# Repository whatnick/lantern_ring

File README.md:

# Lantern Ring

**One ring to rule them all, in the light bind them**

## v2 physical hardware

[FreeCAD v2 twist-lock hardware](hardware/v2.0/ring_3d/README.md) provides a keyed
30-degree bayonet PCB/battery cassette, opposite-face CR2032 pogo contacts,
one insulated ground lead and screw-retained battery access. The compact crown
is 24.9 mm across, with the original 11 mm band width at the crest and a **rounded open-bottom
elastic band**. Hollow 40-degree conical shoulder walls brace the crown onto the
band, as the legacy side plates did. The shank tapers to 6 mm at the open tips
with comfort-fit rounded edges, using 2.5% less material than the unbraced band. The crown nests onto the finger arc; its LED-inclusive profile
is **11.42 mm above the finger**. A
[same-scale legacy comparison](hardware/v2.0/ring_3d/generated/legacy-comparison.png)
documents the remaining height/diameter difference. Editable CAD and printable
files are included.
Battery replacement needs no soldering; the direct positive pogo and ground
lead still need three permanent joints. This is an unprinted, electrically unqualified prototype for the
mono-colour PCB, not a certified battery-powered product.
The [elastic-fit study](hardware/v2.0/ring_3d/generated/flex-fit.png) illustrates
a 1 mm expansion target, not a qualified size range; PA12 spring-back, creep
and comfortable fit still require physical testing.

### v2 CAD renders

Blender 5 assembly animation ([MP4](hardware/v2.0/ring_3d/generated/lantern_ring_v2_assembly.mp4)).

Low-profile [Lantern Corps crowns](hardware/v2.0/ring_3d/README.md#lantern-corps-crowns-low-profile-top-piece):
swappable translucent top pieces that sit 2.3 mm above the PCB (the v1 emblem stood 6.5 mm).

Crown swap animation ([MP4](hardware/v2.0/ring_3d/generated/lantern_corps_swap.mp4)),
with each crown and LED colour representing a different Corps.

| Assembled: low crown, braced open tapered band | Exploded: bayonet cassette and pogo stack |
| --- | --- |
|  |  |

| Same-scale legacy comparison | Open-band elastic-fit screen (unqualified) |
| --- | --- |
|  |  |

[Repository baseline review](docs/design/repository-review.md) distinguishes the
existing board variants and unfinished experiments.

[Contact and metal-body roadmap](docs/design/contact-roadmap/README.md) explores
copper-tape pressure contacts, replaceable plated springs and an electrically
isolated metal shell, with progressive local renders and prepared Nano Banana
prompts. These concepts do not replace the current manufacturing CAD.

[IR ring programming clip](hardware/v2.0/ring_ir_prog_clip/README.md) is a
solder-free pogo-pin ISP clip for the ATtiny85 `ring_pcb_IR`. It is a probe,
anvil and fence PCB set for an Adafruit 5434-style hinged clip kit. Its pin
spacing comes from the IR board's rear test pads, and it has a standard AVR
ISP-6 header. It passes KiCad ERC/DRC and a FreeCAD virtual fit against
estimated clip dimensions. It has not yet been built or measured.

### Experimental RGBW PCBs

The [four-single-MOSFET](hardware/v2.0/ring_pcb_RGBW/README.md) and
[two-dual-MOSFET](hardware/v2.0/ring_pcb_RGBW_dual/README.md) RGBW variants
are both routed as **four-layer, 1.6 mm** boards. Their inner layers are GND
and VCC planes; the IR outline, TP1-TP9 pads and exposed contact windows are
preserved. Saved KiCad ERC/DRC reports show zero violations, unconnected items
and schematic-parity issues. See the [routing and MOSFET comparison](docs/design/rgbw-mosfet-comparison.md).

These are virtual results, not fabrication, physical clip-fit, battery safety
or electrical qualification. [Experimental RGBW firmware](firmware/rgbw-driver/README.md)
provides fixed and JP1-selected colours but has not been tested on hardware.
The redesigned RGBW LED is active; confirm stock and assembly sourcing before ordering.

The [Elecrow 3D-print feasibility assessment](docs/design/elecrow-3d-print-feasibility.md)
covers fit risks for the ring's non-PCB components.

The [Lantern Ring pricing and market feasibility analysis](docs/design/product-market-analysis.md)
documents the unit-cost assumptions, price tests, event-market scenarios and
commercial readiness gates.

Engineering source references and regeneration instructions are in
[development.md](development.md).
| 1. Serviceable pogo | 2. Copper pressure | 3. Plated springs | 4. Floating metal |
| --- | --- | --- | --- |
|  |  |  |  |

## Legacy printed ring bodies

These are earlier printed ring bodies and emblem pieces, not the v2 twist-lock
cassette. The [legacy ring-body and emblem models](hardware/v1.0/ring_3d/) are
preserved alongside the newer design.

Available on :
- [Tindie](https://www.tindie.com/products/whatnick/lantern-rings/)
- [Etsy](https://www.etsy.com/au/listing/1365896916/lantern-corps-cosplay-ring-with)
- [PCBWay]
- [OSHPark]
- [Aisler](https://aisler.net/p/UOBXJDJP)
- [Shapeway](https://www.shapeways.com/shops/whatnick)
  - [Ring body](https://www.shapeways.com/product/PLQWLUV6V/lantern-ring-body?optionId=251926151&li=shop-inventory)
  - [Green Lantern Logo](https://www.shapeways.com/product/PLQWLUV6V/lantern-ring-body?optionId=251926155&li=shop-inventory)
  - [Yellow Lantern Logo](https://www.shapeways.com/product/87AK6SYQN/yellow-fear-lanterns-logo-from-dc-universe?optionId=253809626&li=shops)
  - [Blue Lantern Logo](https://www.shapeways.com/product/LDGX3RYWW/hope-lanterns-logo-from-dc-universe?optionId=253809602&li=shops)
  - [Indigo Lantern Logo](https://www.shapeways.com/product/RX6YYCM8E/indigo-empathy-logo-from-dc-universe?optionId=253810127&li=shops)
  - [Violet Lantern Logo](https://www.shapeways.com/product/Q4ZM3RG58/purple-love-lanterns-logo?optionId=253810197&li=shops)
  - [Red Lantern Logo](https://www.shapeways.com/product/2T2WC596J/red-rage-lanterns-logo?optionId=253810042&li=shops)
  - [Orange Lantern Logo](https://www.shapeways.com/product/XHF33N3QN/orange-avarice-lanterns-logo?optionId=253810121&li=shops)
  - [Black Lantern Logo](https://www.shapeways.com/product/NEF64B7SB/lantern-ring-life-and-death)
  - [White Lantern Logo](https://www.shapeways.com/product/NEF64B7SB/lantern-ring-life-and-death)
  - [Black MTG Logo](https://www.shapeways.com/product/NJ25J3LPM/magic-the-gathering-black-mana-logo?optionId=253809132)

[LED Colours and quantum physics](https://www.forbes.com/sites/chadorzel/2019/07/01/the-mostly-quantum-physics-of-making-colors/?sh=2ce5846e3953) are inextricably linked.
After watching a temperature based LED colour changing demo at questacon, an idea started forming in my head for using a similar idea with LED's of different colours and seeing how they
react spectrally with temperature.

I have also always been a Green Lantern nerd and I have been making lantern rings since 2010. You will probably find some of them in the wild in Hobart among the clientele of various
pubs and nightclubs. This is a more serious attempt at making a piece of electronic jewellery, cosplay prop and nerdy onanism all rolled into one.

## Licence

[OSHW TAPR](https://tapr.org/the-tapr-open-hardware-license/)

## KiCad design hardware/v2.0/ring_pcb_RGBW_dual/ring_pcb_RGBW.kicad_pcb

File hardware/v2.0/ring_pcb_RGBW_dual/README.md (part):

# Lantern Ring v2 RGBW variant: dual MOSFET option

**Experimental RGBW hardware, not physically qualified.** This generated KiCad
10 project uses one four-die RGBW LED and four MOSFET-driven channels using
two dual N-channel MOSFET packages. It keeps the IR board's native outline,
1.6 mm thickness and TP1-TP9 interface. The RGBW
variant uses **four copper layers**, unlike the two-layer IR board: dedicated
In1 GND and In2 VCC planes avoid relying on fragmented outer pours.
The IR board, programming clip and legacy firmware remain unchanged.

This **routed four-layer** option's saved all-severity KiCad reports show zero
ERC/DRC findings, unconnected items and schematic-parity issues. The separately
retained [four-single-MOSFET option](../ring_pcb_RGBW/README.md) is the
comparison baseline. Both are experimental and neither has been physically
qualified.
[See the routed/electrical comparison](../../../docs/design/rgbw-mosfet-comparison.md).

[Schematic PDF](generated/schematic.pdf) |
[Top render](generated/top.png) | [Rear render](generated/bottom.png) |
[Top routing](generated/top_routing.svg) |
[Rear routing, mirrored for viewing](generated/bottom_routing.svg) |
[Inner GND](generated/ground_plane.svg) | [Inner VCC](generated/supply_plane.svg) |
[Validation evidence](generated/validation.json)

## Fixed mechanical and programming interface

Use the native [IR PCB](../ring_pcb_IR/ring_pcb_IR.kicad_pcb) as the exact
interface source, not a redraw or an assumed circular envelope.

- Preserve all Edge.Cuts geometry, board thickness (1.6 mm), origin and
  orientation. Do not resize or mirror the board.
- Preserve TP1-TP9 positions, pad shapes/sizes, copper sides, exposed mask
  geometry and electrical assignments, including front TP8 GND for the anvil.
  PB3/PB4 becoming application signals does not change TP4/TP5 assignments.
- Preserve the rear pogo grid (3.05 mm) and off-grid TP9 VCC. Do not substitute
  the ISP header's 2.54 mm pitch for the pogo spacing.
- Reuse the existing [v0.2 programming clip](../ring_ir_prog_clip/README.md)
  and [ArduinoISP harness](../ring_ir_prog_clip/programming.md) without
  rewiring. J1 pins 1-6 remain MISO, VCC, SCK, MOSI, RESET, GND.
- Keep rear contact areas clear of components and preserve front anvil
  contact/clearance regions. The new LED and MOSFET envelopes must be checked
  against the clip window and jaws; matching the outline alone does not prove fit.

The existing [board-layer export](../ring_ir_prog_clip/generated/assembly/ir_board_layers.json)
and [clip geometry](../ring_ir_prog_clip/generated/geometry.json) document
the current interface. The native IR board is authoritative if exports differ.
Do not regenerate the clip to accommodate moved RGBW programming pads.

## ATtiny85 pin allocation

Keep the internal oscillator and PB5 RESET enabled so the same ISP clip works.
The ATtiny85 has three usable independent hardware-PWM output pins for this
allocation, not four: Timer1's complementary outputs are not extra independent
colour channels.

| MCU pin | Existing pad | Circuit use | PWM or input |
| --- | --- | --- | --- |
| PB0 | TP1 / MOSI | Red MOSFET gate | Hardware OC0A |
| PB1 | TP2 / MISO | Green MOSFET gate | Hardware OC0B |
| PB2 | TP3 / SCK | White MOSFET gate | Timer-driven software PWM |
| PB3 | TP4 | Optional colour/mode selector | Digital input or ADC3 |
| PB4 | TP5 | Blue MOSFET gate | Hardware OC1B |
| PB5 | TP6 / RESET | ISP reset only | Do not reclaim as GPIO |
| GND | TP7, TP8 | Ground; TP8 is the anvil contact | Unchanged |
| VCC | TP9 | Programming supply | Unchanged |

Yes, a jumper can select colour: PB3 with a pull-up and a separate jumper or
solder bridge to GND provides two selectable presets/modes. Do not alter the
TP4 pogo pad to make the selector. More choices could use a resistor-coded
ADC3 input with defined voltage bands; this needs tolerance/noise validation.
Read/latch the selector before starting PWM and never leave the input floating.
Without a selector, new firmware can define the palette and sweep behaviour.

Reference: [manufacturer ATtiny25/45/85 datasheet, 2586Q](https://ww1.microchip.com/downloads/en/DeviceDoc/Atmel-2586-AVR-8-bit-Microcontroller-ATtiny25-ATtiny45-ATtiny85_Datasheet.pdf),
Table 10-3, page 60. PB4 is OC1B; PB3 is its complementary output and ADC3.
Timer1 OC1A shares PB1, already used by OC0B. PB2 has no hardware PWM output.

## Implemented circuit

The [QT Brightek QBLP679-RGBCW](https://www.qt-brightek.com/datasheet/QBLP679-RGBXW.pdf)
has four independent dies, not an internally common anode. Copper connects
R/G/B/W anodes 5/6/7/8 to VCC; their cathodes are 4/3/2/1. This gives
common-anode circuit operation with the existing low-side N-MOSFETs. The
5 x 5 x 1.65 mm package has a 5.5 mm lead span; the footprint follows the
manufacturer's page 11 land pattern. Page 4 brightness specifications are
at 20 mA and do not predict this design's sub-mA brightness or colour.

On 22 November 2026 DigiKey listed this exact part active and in stock in cut
tape; JLCPCB listed it out of stock. Recheck availability, MSL 5A handling,
assembly sourcing and current price before ordering.

Each cathode connects through a **2.2k, 1%, 63 mW 0402** resistor to one
channel of an onsemi **NTZD3154NT1G** dual N-channel MOSFET (SOT-563).
Q1 drives R/G and Q2 drives B/W. Each source goes to GND; every gate retains
its own 1k series resistor and 100k pull-down. Onsemi specifies RDS(on) maximum
0.9 ohm at VGS 1.8 V/ID 350 mA and absolute VGS +/-7 V. Pin mapping is
1=S1, 2=G1, 3=D2, 4=S2, 5=G2, 6=D1; verify the manufacturer pinout before
substitution. The manufacturer lists NTZD3154NT1G active in its ordering table
but marks some other suffixes discontinued; confirm actual purchasing status.
The MCU is **ATTINY85-20MU**, with 100n X7R 10 V local bypass, 10u X5R 10 V
bulk capacitance and a 10k RESET pull-up. The [BOM](generated/bom.csv) records
MPNs and distributor search links, not stock or purchase approval.

JP1 is a separate, normally open **0402 bridge footprint**: short it with a
0-ohm 0402 link or a deliberate solder bridge to pull PB3 low. Its external
100k pull-up defines the open state. It is not a fitted pin header and does
not modify TP4. Two settings select two firmware-defined presets/modes; an
ADC ladder for more choices is not implemented.

At the maximum intended 5.5 V bench supply, even a shorted die is bounded by
`5.5 / (2200 * 0.99) = 2.526 mA` per channel. Maximum resistor dissipation is
13.9 mW, below 63 mW. These are conservative electrical bounds, **not CR2032
load/temperature qualification**. ISP can switch the R/G/W gates while RESET
is asserted; firmware cannot prevent that. The resistors remain in circuit.
Use one regulated 5 V programming supply with matching logic levels; remove
the CR2032, never backfeed or charge it. Do not apply 5 V while a cell is fitted.

There is **no boost converter or constant-current driver**. Blue/green/white
may dim or extinguish as the cell discharges. Measure brightness, simultaneous
channel current, battery life and temperatures before treating this as usable
jewellery. The NTZD3154N gate network also loads the ISP signals; verify actual
programming on the new assembled variant rather than inheriting the IR result.

## Firmware boundary

- The working 5 V programming report applies to the IR board, not automatically
  this RGBW circuit. Check every new component, LED current limiter and rail for
  the 5 V programming case. Remove the CR2032; never join programming and cell
  supplies or charge the cell.
- Budget total LED/MCU current for a primary CR2032, including simultaneous
  colours. Its resistance is not a current limiter. Blue/green/white forward
  voltage may leave insufficient regulation headroom as the cell discharges;
  determine whether a boost rail is needed before choosing parts.
- Use new RGBW firmware, not edits to Arduino-TV-B-Gone. Preserve timer ownership
  for three hardware channels and timer-driven software PWM on PB2; validate
  PWM frequency, endpoint duties, core timing interactions and colour mixing.
  Keep PB3 configured as an input and preserve RESET/SPI fuses.

An [experimental RGBW driver](../../../firmware/rgbw-driver/README.md) now
provides a fixed firmware colour or two JP1-selected presets. It has not been
flashed or validated on this PCB. Validate polarity, frequencies, endpoint
duties, current and selector latching on real hardware.

## Sources, rebuild and checks

`parameters.json` defines placements, channel/pin mapping, exact LED lands,
critical VCC/PB2 routes and via positions. `generate.py` reads the native IR board,
generates the schematic and exports KiCad's actual XML netlist before assigning
PCB nets. Edit these sources, **not generated KiCad files**. `finish_route.py`
requires the matching placement/DSN and imports the local SES before refilling
and checking the saved board with KiCad. No electrical-rule exclusions are used.
The four-layer stack must be fabricated at 1.6 mm finished thickness.

```powershell
# Verify saved work without discarding routing:
& hardware\v2.0\ring_pcb_RGBW_dual\build.ps1

# Complete regeneration, local routing, CAD and actual-board renders:
& hardware\v2.0\ring_pcb_RGBW_dual\build.ps1 -Rebuild -Render -FreeroutingJar 'C:\tools\freerouting-2.5.0.jar'

python -m unittest discover -s hardware\v2.0\ring_pcb_RGBW_dual -p test_rgbw.py
```

Requires KiCad 10, FreeCAD's bundled Python and Java for regeneration.
Paths can be overridden with the build parameters. Freerouting 2.5.0 runs
locally with analytics, API and MCP servers off and isolated settings.
The generator first connects supply pads to the inner planes with checked
0.25 mm stubs and places the constrained PB2/SCK escape. The build rejects
any unconnected GND/VCC item before routing. Autorouting handles the remaining
signals; it skips the already connected Power class. This is not a native
electrical-rule exclusion. Router fanout, optimization and automatic neck-down
are disabled; final native DRC rejects any route narrower than 0.15 mm.
Power is 0.25 mm; through-vias are 0.45/0.20 mm diameter/drill.
The footprint is assembly-dense: references use 0.6 mm text/0.12 mm stroke
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
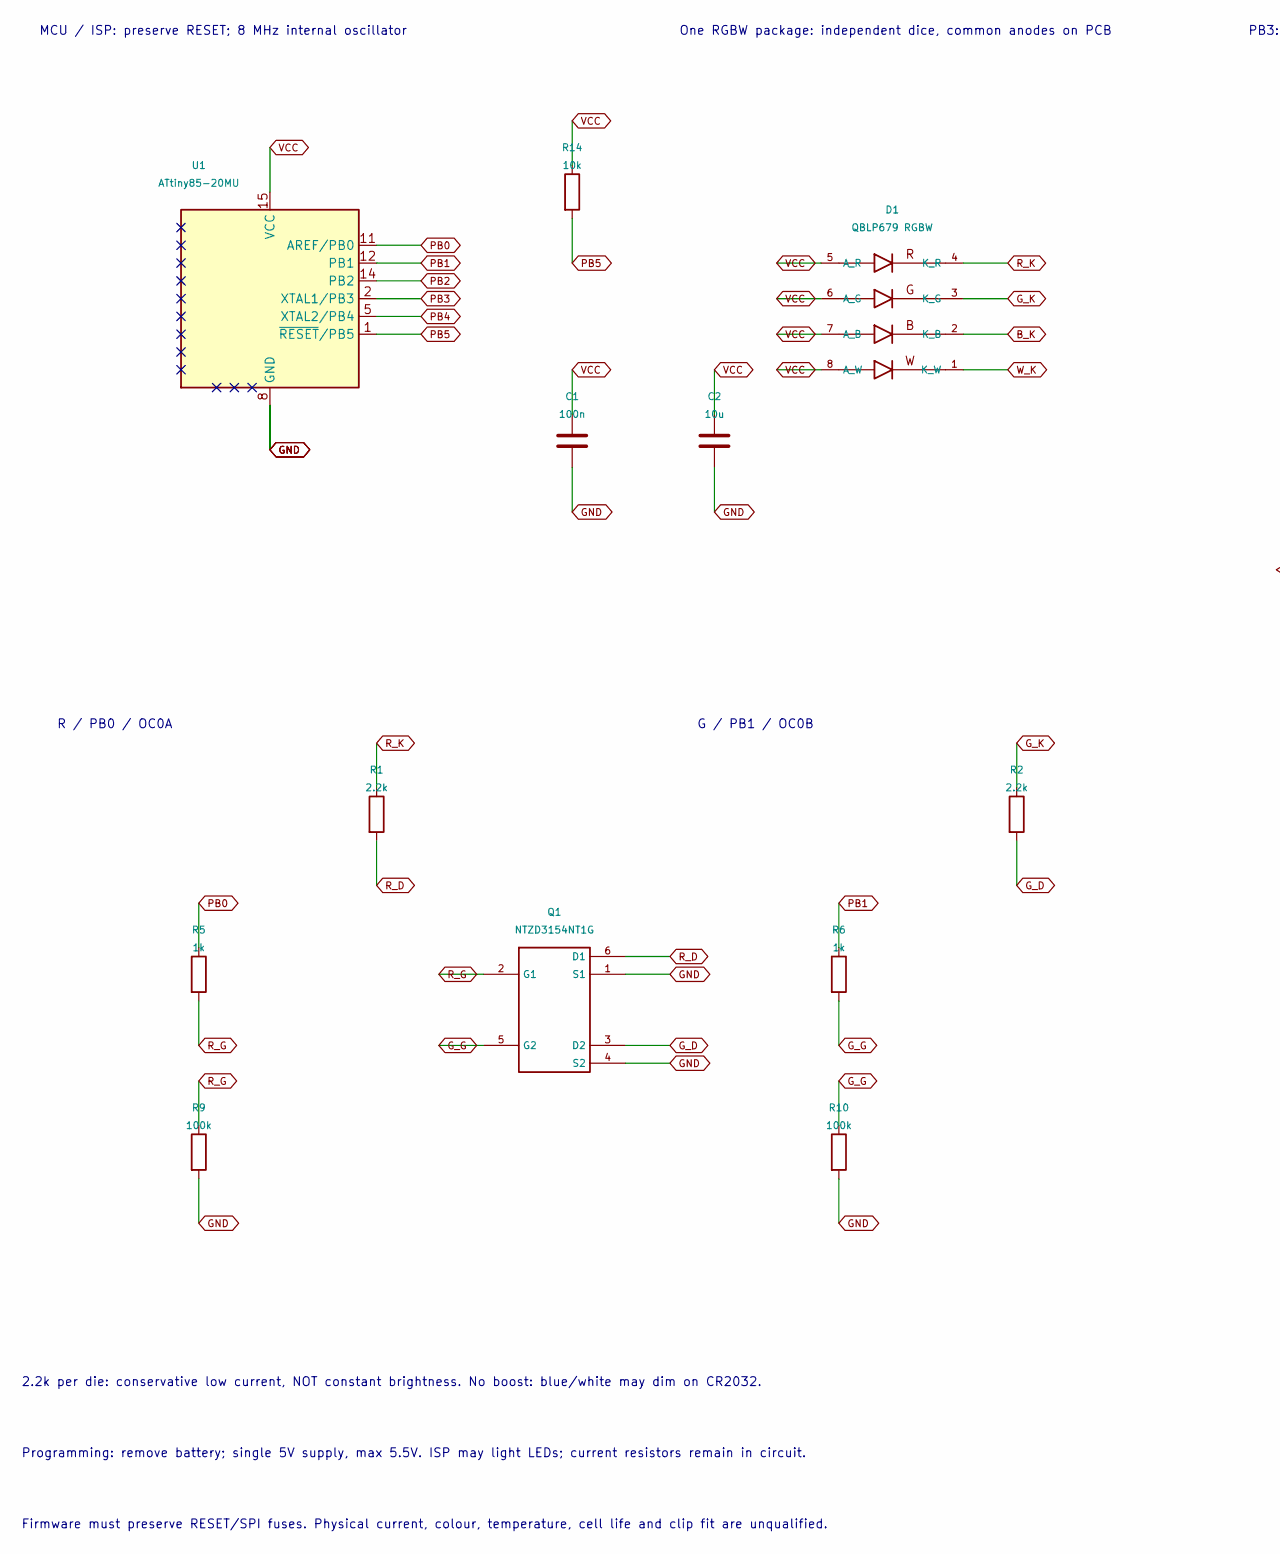
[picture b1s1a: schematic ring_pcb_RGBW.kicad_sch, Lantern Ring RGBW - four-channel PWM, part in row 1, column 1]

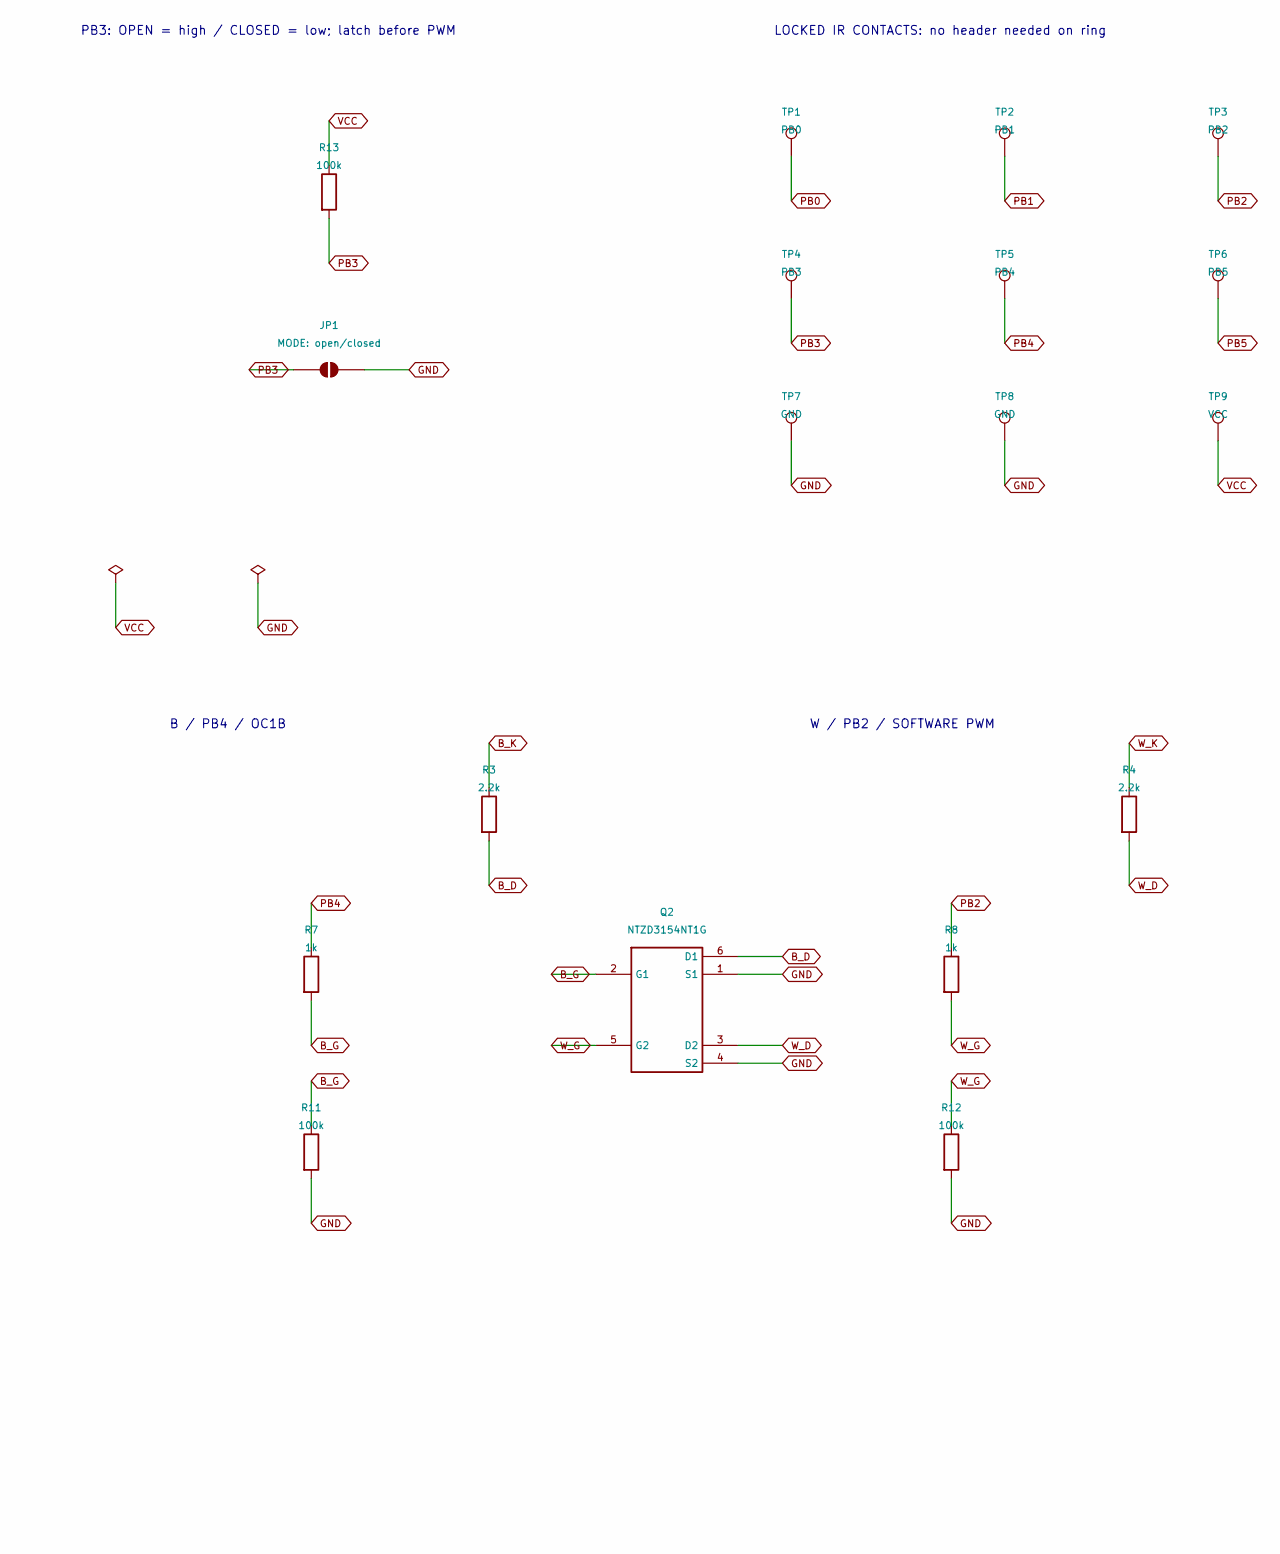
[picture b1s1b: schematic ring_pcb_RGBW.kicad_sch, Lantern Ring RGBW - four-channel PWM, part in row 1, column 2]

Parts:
C1: 100n; C0402; MPN GRM155R71A104KA01D
C2: 10u; C0805; MPN CL21A106KPFNNNE
D1: QBLP679 RGBW; QBLP679_PLCC8; MPN QBLP679-RGBCW
JP1: MODE: open/closed; ModeBridge
Q1, Q2: NTZD3154NT1G; SOT563; MPN NTZD3154NT1G
R1, R2, R3, R4: 2.2k; R0402; MPN RC0402FR-072K2L
R5, R6, R7, R8: 1k; R0402; MPN RC0402FR-071KL
R9, R10, R11, R12, R13: 100k; R0402; MPN RC0402FR-07100KL
R14: 10k; R0402; MPN RC0402FR-0710KL
TP1: PB0; IR_TP1
TP2: PB1; IR_TP2
TP3: PB2; IR_TP3
TP4: PB3; IR_TP4
TP5: PB4; IR_TP5
TP6: PB5; IR_TP6
TP7: GND; IR_TP7
TP8: GND; IR_TP8
TP9: VCC; IR_TP9
U1: ATtiny85-20MU; QFN20; MPN ATTINY85-20MU

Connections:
B_D: Q2.6 (D1), R3.2
B_G: Q2.2 (G1), R7.2, R11.1
B_K: D1.2 (K_B), R3.1
GND: C1.2, C2.2, JP1.2 (B), Q1.1 (S1), Q1.4 (S2), Q2.1 (S1), Q2.4 (S2), R9.2, R10.2, R11.2, R12.2, TP7.1, TP8.1, U1.8 (GND), U1.21 (GND)
G_D: Q1.3 (D2), R2.2
G_G: Q1.5 (G2), R6.2, R10.1
G_K: D1.3 (K_G), R2.1
PB0: R5.1, TP1.1, U1.11 (AREF/PB0)
PB1: R6.1, TP2.1, U1.12 (PB1)
PB2: R8.1, TP3.1, U1.14 (PB2)
PB3: JP1.1 (A), R13.2, TP4.1, U1.2 (XTAL1/PB3)
PB4: R7.1, TP5.1, U1.5 (XTAL2/PB4)
PB5: R14.2, TP6.1, U1.1 (~RESET/PB5)
R_D: Q1.6 (D1), R1.2
R_G: Q1.2 (G1), R5.2, R9.1
R_K: D1.4 (K_R), R1.1
VCC: C1.1, C2.1, D1.5 (A_R), D1.6 (A_G), D1.7 (A_B), D1.8 (A_W), R13.1, R14.1, TP9.1, U1.15 (VCC)
W_D: Q2.3 (D2), R4.2
W_G: Q2.5 (G2), R8.2, R12.1
W_K: D1.1 (K_W), R4.1

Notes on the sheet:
MCU / ISP: preserve RESET; 8 MHz internal oscillator
One RGBW package: independent dice, common anodes on PCB
PB3: OPEN = high / CLOSED = low; latch before PWM
LOCKED IR CONTACTS: no header needed on ring
R / PB0 / OC0A
G / PB1 / OC0B
B / PB4 / OC1B
W / PB2 / SOFTWARE PWM
2.2k per die: conservative low current, NOT constant brightness. No boost: blue/white may dim on CR2032.
Programming: remove battery; single 5V supply, max 5.5V. ISP may light LEDs; current resistors remain in circuit.
Firmware must preserve RESET/SPI fuses. Physical current, colour, temperature, cell life and clip fit are unqualified.

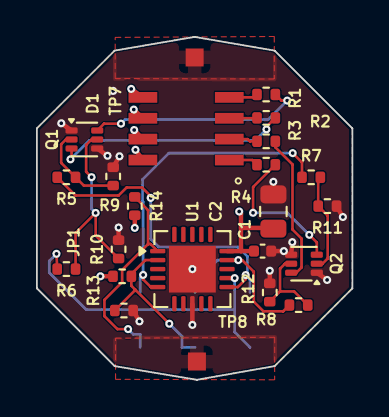
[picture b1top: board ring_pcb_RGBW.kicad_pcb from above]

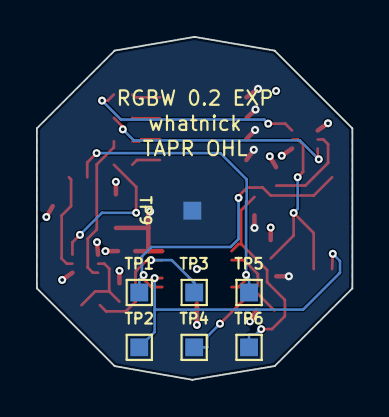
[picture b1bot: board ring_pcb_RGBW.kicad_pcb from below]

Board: 4 copper layers, 17.5 x 19.1 mm, 30 parts (7 on the bottom side), 20 nets.

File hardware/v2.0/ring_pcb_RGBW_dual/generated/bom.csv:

Reference,Value,Footprint,Manufacturer,MPN,Description,DigiKey,Mouser,Datasheet
U1,ATtiny85-20MU,ring_rgbw:QFN20,Microchip,ATTINY85-20MU,"ATtiny85 8KB, QFN20 exposed pad, 2.7-5.5 V",https://www.digikey.com/en/products?keywords=ATTINY85-20MU,https://www.mouser.com/c/?q=ATTINY85-20MU,https://ww1.microchip.com/downloads/en/DeviceDoc/Atmel-2586-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
D1,QBLP679 RGBW,ring_rgbw:QBLP679_PLCC8,QT Brightek,QBLP679-RGBCW,"Four independent dies, anodes joined on PCB; 5.0x5.0x1.65 mm",https://www.digikey.com/en/products?keywords=QBLP679-RGBCW,https://www.mouser.com/c/?q=QBLP679-RGBCW,https://www.qt-brightek.com/datasheet/QBLP679-RGBXW.pdf
R1,2.2k,ring_rgbw:R0402,YAGEO,RC0402FR-072K2L,R die current limiter; 0402 1% 63mW,https://www.digikey.com/en/products?keywords=RC0402FR-072K2L,https://www.mouser.com/c/?q=RC0402FR-072K2L,
R5,1k,ring_rgbw:R0402,YAGEO,RC0402FR-071KL,R gate/ISP isolation; 0402 1% 63mW,https://www.digikey.com/en/products?keywords=RC0402FR-071KL,https://www.mouser.com/c/?q=RC0402FR-071KL,
R9,100k,ring_rgbw:R0402,YAGEO,RC0402FR-07100KL,R gate pull-down; 0402 1% 63mW,https://www.digikey.com/en/products?keywords=RC0402FR-07100KL,https://www.mouser.com/c/?q=RC0402FR-07100KL,
R2,2.2k,ring_rgbw:R0402,YAGEO,RC0402FR-072K2L,G die current limiter; 0402 1% 63mW,https://www.digikey.com/en/products?keywords=RC0402FR-072K2L,https://www.mouser.com/c/?q=RC0402FR-072K2L,
R6,1k,ring_rgbw:R0402,YAGEO,RC0402FR-071KL,G gate/ISP isolation; 0402 1% 63mW,https://www.digikey.com/en/products?keywords=RC0402FR-071KL,https://www.mouser.com/c/?q=RC0402FR-071KL,
R10,100k,ring_rgbw:R0402,YAGEO,RC0402FR-07100KL,G gate pull-down; 0402 1% 63mW,https://www.digikey.com/en/products?keywords=RC0402FR-07100KL,https://www.mouser.com/c/?q=RC0402FR-07100KL,
R3,2.2k,ring_rgbw:R0402,YAGEO,RC0402FR-072K2L,B die current limiter; 0402 1% 63mW,https://www.digikey.com/en/products?keywords=RC0402FR-072K2L,https://www.mouser.com/c/?q=RC0402FR-072K2L,
R7,1k,ring_rgbw:R0402,YAGEO,RC0402FR-071KL,B gate/ISP isolation; 0402 1% 63mW,https://www.digikey.com/en/products?keywords=RC0402FR-071KL,https://www.mouser.com/c/?q=RC0402FR-071KL,
R11,100k,ring_rgbw:R0402,YAGEO,RC0402FR-07100KL,B gate pull-down; 0402 1% 63mW,https://www.digikey.com/en/products?keywords=RC0402FR-07100KL,https://www.mouser.com/c/?q=RC0402FR-07100KL,
R4,2.2k,ring_rgbw:R0402,YAGEO,RC0402FR-072K2L,W die current limiter; 0402 1% 63mW,https://www.digikey.com/en/products?keywords=RC0402FR-072K2L,https://www.mouser.com/c/?q=RC0402FR-072K2L,
R8,1k,ring_rgbw:R0402,YAGEO,RC0402FR-071KL,W gate/ISP isolation; 0402 1% 63mW,https://www.digikey.com/en/products?keywords=RC0402FR-071KL,https://www.mouser.com/c/?q=RC0402FR-071KL,
R12,100k,ring_rgbw:R0402,YAGEO,RC0402FR-07100KL,W gate pull-down; 0402 1% 63mW,https://www.digikey.com/en/products?keywords=RC0402FR-07100KL,https://www.mouser.com/c/?q=RC0402FR-07100KL,
Q1,NTZD3154NT1G,ring_rgbw:SOT563,onsemi,NTZD3154NT1G,Dual low-side MOSFET; Rds max 0.9 ohm at Vgs=1.8 V,https://www.digikey.com/en/products?keywords=NTZD3154NT1G,https://www.mouser.com/c/?q=NTZD3154NT1G,https://www.onsemi.com/pdf/datasheet/ntzd3154n-d.pdf
Q2,NTZD3154NT1G,ring_rgbw:SOT563,onsemi,NTZD3154NT1G,Dual low-side MOSFET; Rds max 0.9 ohm at Vgs=1.8 V,https://www.digikey.com/en/products?keywords=NTZD3154NT1G,https://www.mouser.com/c/?q=NTZD3154NT1G,https://www.onsemi.com/pdf/datasheet/ntzd3154n-d.pdf
R13,100k,ring_rgbw:R0402,YAGEO,RC0402FR-07100KL,Mode selector pull-up; 0402 1% 63mW,https://www.digikey.com/en/products?keywords=RC0402FR-07100KL,https://www.mouser.com/c/?q=RC0402FR-07100KL,
R14,10k,ring_rgbw:R0402,YAGEO,RC0402FR-0710KL,ISP RESET pull-up; 0402 1% 63mW,https://www.digikey.com/en/products?keywords=RC0402FR-0710KL,https://www.mouser.com/c/?q=RC0402FR-0710KL,
C1,100n,ring_rgbw:C0402,Murata,GRM155R71A104KA01D,100nF X7R 10V 0402 local decoupling,https://www.digikey.com/en/products?keywords=GRM155R71A104KA01D,https://www.mouser.com/c/?q=GRM155R71A104KA01D,
C2,10u,ring_rgbw:C0805,Samsung Electro-Mechanics,CL21A106KPFNNNE,10uF X5R 10V 0805 bulk; verify DC bias,https://www.digikey.com/en/products?keywords=CL21A106KPFNNNE,https://www.mouser.com/c/?q=CL21A106KPFNNNE,

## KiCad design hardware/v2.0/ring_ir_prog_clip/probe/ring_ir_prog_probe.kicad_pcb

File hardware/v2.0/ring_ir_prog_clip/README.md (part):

# Ring IR programming clip

[Illustrated HTML wiring and voltage-testing reference](../../../docs/arduino-isp-wiring-reference.html)
contains the PDF's cable map, physical parts, Arduino IDE setup and front-side
C1/C2 checks. Open the downloaded HTML in a browser with its `docs/images` assets.

A solder-free in-system programming (ISP) clip for the
[`ring_pcb_IR`](../ring_pcb_IR) ATtiny85 board. Spring-loaded pogo pins press on
the board's rear test pads, held by a hinged clip like
[Adafruit 5434](https://www.adafruit.com/product/5434) but with pin spacing
matched to the ring. The parts are the jaws, spring and hardware from the
[AliExpress DIY pogo clip kit](https://www.aliexpress.com/item/1005006153573416.html),
with its generic guide PCBs replaced by the boards here.

> **Status: custom IR clip built and physical fit tested (user-reported).**
> ERC and DRC pass with zero violations of any severity. The FreeCAD fit check
> passes against a clip model built from **photo and datasheet estimates**,
> because the seller publishes no drawing. The AliExpress kit has now been
> assembled and photographed with calipers. The new reconstruction below uses
> readable measurements, but mounting geometry and spring travel remain estimates.
> New album photographs show the assembled custom clip with the IR PCB seated.
> No measured fit dimensions or contact-quality data have been recorded yet.
> A 2026-11-10 ATtiny85 programming run completed with full flash readback
> verification after contact alignment. The user reports the 5 V target rail
> working in practice; the documented Uno harness now uses 5 V power.
> This does not qualify contact life, LED current/temperature or mechanical
> retention; the original PCB fit report remains a virtual estimate.

## In-place minor revision

v0.2 **overwrites the existing design paths**, not a second versioned project:
`probe/ring_ir_prog_probe.kicad_pcb`, `anvil/ring_ir_prog_anvil.kicad_pcb` and
`fence/ring_ir_prog_fence.kicad_pcb`, with the existing probe/anvil schematics
and projects. Keep these names; do not create parallel `v0.2` files/directories.
The screws and balanced GND pads are a minor revision of the same assembly,
not a changed ISP pinout. Edit the generator/configuration and rebuild in place.
Git history preserves earlier revisions; old photos/quote packages remain historical.

[Recorded programming evidence](programming-evidence.json) and the
[`lantern-ring-ir-programming` skill](../../../.github/skills/lantern-ring-ir-programming/SKILL.md)
document the actual successful flow.

## As-built clip with IR PCB

The latest user-supplied photographs in the
[Clip Programmer Assembly album](https://photos.google.com/share/AF1QipNwx2ELJVqs2tECPYQ5cwoX293osVatVeGoo2XyBIm2Dzrf3vpLs3F5LxYhLjrQvA?key=RVRZOGVPc3RqZ1FpdEt0eEJ4c1piN01uNm1QZm9n),
reviewed on 2026-11-10, show the purple probe/guide PCBs assembled on the clip,
the IR board seated rear-side up in the lower locator, and pogo tips meeting
the visible rear test-pad region, including the off-grid VCC pad.
These are photographs of hardware, not CAD renders.

| Rear test-pad close-up | Off-grid VCC and signal-pad close-up |
| --- | --- |
|  |  |

The pictures support the reported physical assembly and seating; they do not
establish every tip's alignment, contact resistance, preload, retention or
successful programming. J1's SMD header lands are visibly unpopulated in these
three earlier views, so they are not evidence of a complete programmer connection. The photographed PCB
revision is not verified, and these images do not validate the new v0.2
anvil/fence screw holes or paired GND contacts. Their source URLs and downloaded
file hashes are preserved in [image provenance](images/sources.json).
No CAD dimensions or measured/unmeasured flags were changed from these views.

The newer photograph below shows the Uno, loose programming cable and the clip
with its J1 header fitted. The female leads are **not plugged into the clip**.
Use the [colour-coded harness diagrams and editable Fritzing sketch](programming.md#colour-coded-arduinoisp-harness)
to wire by signal and pin number, not by guessing colours from the photograph.

## Kit assembly animation

[Assembly video (MP4)](generated/assembly/clip_assembly.mp4) shows the lower jaw,
compression spring, upper jaw, hinge, grip block, guide/probe PCBs, screws/nuts,
pogo pins and header coming together, separating, and opening at the hinge.
The main assembly/explosion now uses the **actual custom IR adapter with SMD
header**, not a generic stock probe. A separate comparison shows
**1.27, 2.00 and 2.54 mm** stock-grid studies.
Fine-pitch pins require different guide drills; do not force large pins into them.
The flights apart identify parts, not a collision-verified tool-access sequence.
The final segment shows the **actual KiCad IR PCB copper, solder-mask openings
and silkscreen**, lifted clear for inspection and then seated LEDs-down in the
custom adapter. Component boxes remain clearance envelopes, not detailed package
models.

The custom-adapter segment separates the **actual probe, second probe/guide,
anvil and fence PCBs**, using KiCad-exported STEP substrates and the actual
top-side **SMD 2x3 male header** model, with KiCad copper, mask and silkscreen.
Its 2.54 mm mating posts accept female Dupont programming leads; there are no
header tails projecting below the probe. The pogo pattern remains unchanged.
The black service loop shows the required ground connection:
**ISP J1.6 → probe J2 → insulated wire → anvil J1 → ENIG P8 → front TP8**.
Its flexible shape is illustrative, not a cable-clearance simulation.
PB3/PB4 remain spare, unconnected positions on the probe.

**A stock 2.54 mm pogo grid is not a direct match to this IR board.** Its signal
test pads are on a **3.05 mm grid**, VCC is off-grid, and ground is on the front.
The 2.54 mm AVR ISP *header* pitch must not be confused with pogo spacing.
FreeCAD places a centred 2.54 mm grid optimistically over six pads: outer pin
centres miss by 0.51 mm across and 0.255 mm along the rows (0.570 mm diagonally).
The outer tip faces overlap only about 40% of the nominal pads; this is not
a dependable contact. Extra stock pins and wiring are not assumed safe.
Use the custom seven-pin probe/guide plus the front-ground anvil, not stock PCBs.
Rechecked directly with KiCad's board API: TP1/TP3/TP5 X coordinates are
139.6004/136.5504/133.5004 mm; TP1/TP2 Y coordinates are
115.7986/118.8486 mm. Both differences are **3.0500 mm**. Pads are 1.00 mm square,
so the edge-to-edge gap is 2.05 mm, not 2.54 mm. The reported approximately
2.5 mm physical reading does not match these centre coordinates; confirm the
physical board revision and repeat across multiple centres before changing
the manufactured adapter. The PCB and pad positions have not been altered.

The reconstructed body passes solid/STEP round-trip, all-pair static collision
and 13-position hinge-opening checks for each variant (0 to 6 degrees).
Estimated spring geometry is compressed at each pose and checked for jaw
interference and coil spacing; this is **not** a force or fatigue simulation.
The custom pins nominally cover their pads, but a 0.9 mm tip on a 1 mm pad has
only **0.05 mm** edge margin: physical registration still needs qualification.
Threads, solder joints, spring-end seating and cable clearance are not resolved.
The IR adapter retains the earlier unmeasured P75 length/travel assumptions;
the album's 14.0/16.4 mm loose pins are not interchangeable without a stack rebuild.

| Probe (pin side up, two stacked) | Probe (ring side) | Anvil (lower jaw) | Fence (locator) |
| --- | --- | --- | --- |
|  |  |  |  |

### Current 2D board drawings

| Board | Front | Rear (mirrored viewing side) |
| --- | --- | --- |
| Probe / guide | [Copper + silk SVG](generated/ring_ir_prog_probe_top_2d.svg) | [Copper + silk SVG](generated/ring_ir_prog_probe_bottom_2d.svg) |
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
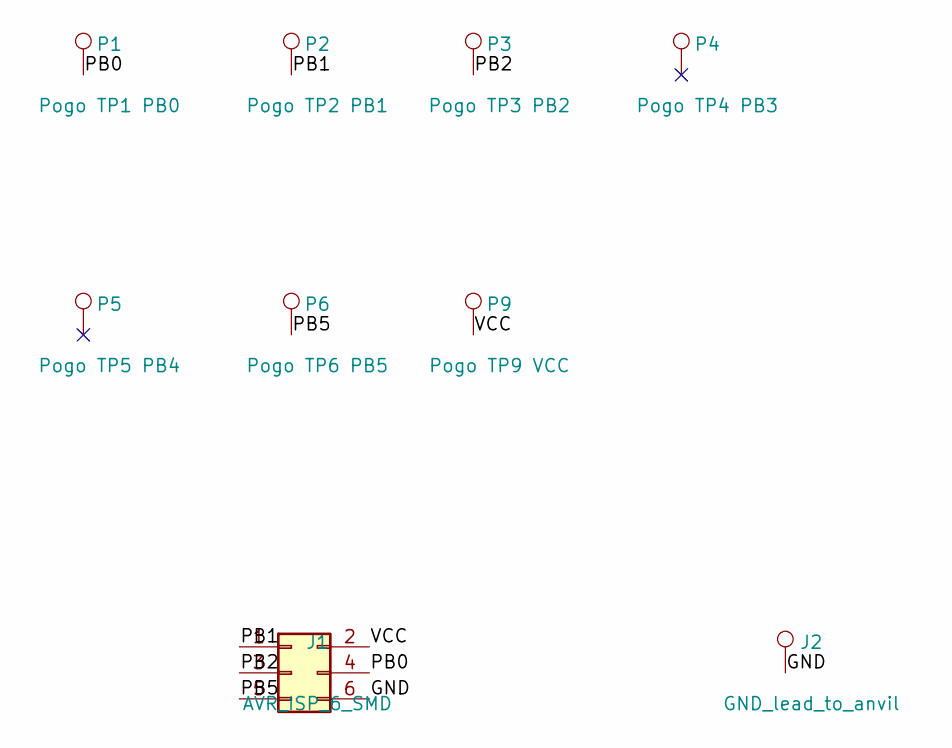
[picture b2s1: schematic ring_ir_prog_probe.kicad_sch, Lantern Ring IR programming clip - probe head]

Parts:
J1: AVR_ISP_6_SMD; PinHeader_2x03_P2.54mm_Vertical_SMD
J2: GND_lead_to_anvil; TestPoint_THTPad_D1.5mm_Drill0.7mm
P1: Pogo TP1 PB0; Pogo_P75_THT
P2: Pogo TP2 PB1; Pogo_P75_THT
P3: Pogo TP3 PB2; Pogo_P75_THT
P4: Pogo TP4 PB3; Pogo_P75_THT
P5: Pogo TP5 PB4; Pogo_P75_THT
P6: Pogo TP6 PB5; Pogo_P75_THT
P9: Pogo TP9 VCC; Pogo_P75_THT

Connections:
/GND: J1.6, J2.1
/PB0: J1.4, P1.1
/PB1: J1.1, P2.1
/PB2: J1.3, P3.1
/PB5: J1.5, P6.1
/VCC: J1.2, P9.1

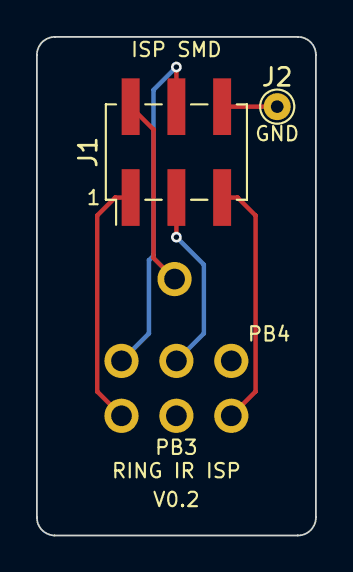
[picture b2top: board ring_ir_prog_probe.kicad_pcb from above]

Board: 2 copper layers, 15.5 x 27.7 mm, 11 parts (0 on the bottom side), 6 nets.

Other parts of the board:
H1, H2: M2_Slot_Clip_Jaw

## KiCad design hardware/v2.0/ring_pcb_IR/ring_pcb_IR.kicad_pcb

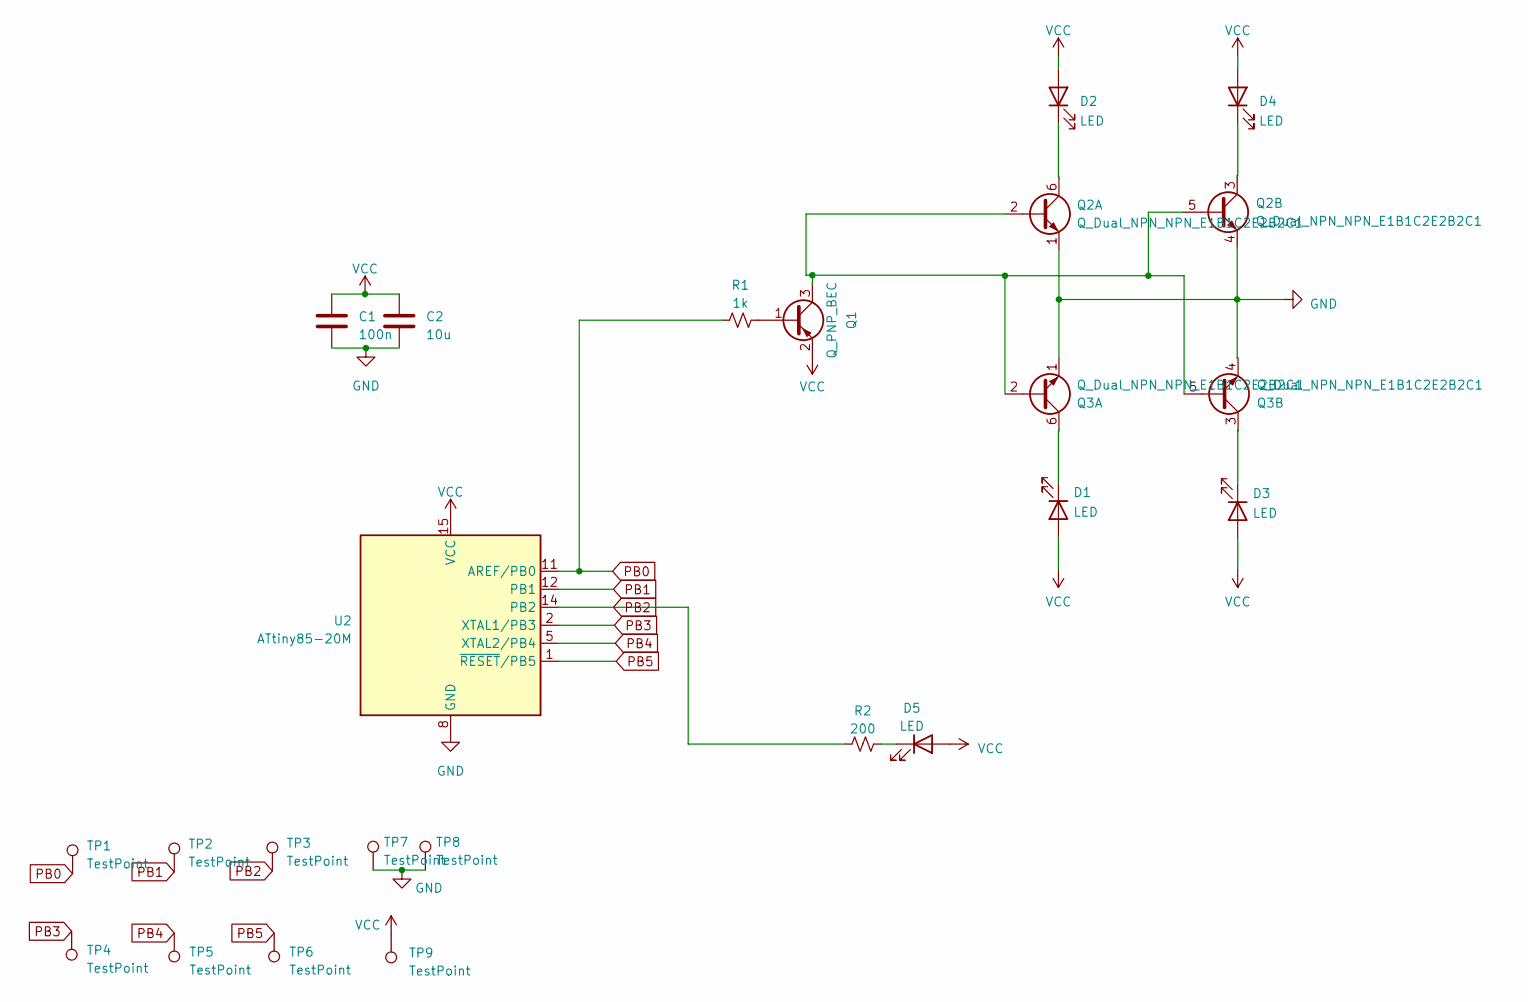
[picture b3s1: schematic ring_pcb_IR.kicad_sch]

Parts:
C1: 100n; C_0603_1608Metric; MPN C0603C104J4RACTU
C2: 10u; C_0603_1608Metric; MPN GRM188R61A106KE69J
D1, D2, D3, D4: LED; LED_0603_1608Metric; MPN 15406094BA500
D5: LED; LED_0603_1608Metric; MPN 150060RS75000
Q1: Q_PNP_BEC; SOT-23; MPN MMBTA55LT1G
Q2, Q3: Q_Dual_NPN_NPN_E1B1C2E2B2C1; SOT-363_SC-70-6; MPN BC847BS,115
R1: 1k; R_0603_1608Metric; MPN RT0603FRE101KL
R2: 200; R_0603_1608Metric; MPN RT0603BRD07210RL
TP1, TP2, TP3, TP4, TP5, TP6, TP7, TP8, TP9: TestPoint; TestPoint_Pad_1.0x1.0mm; MPN DNP
U2: ATtiny85-20M; QFN-20-1EP_4x4mm_P0.5mm_EP2.6x2.6mm; MPN ATTINY85-20MU

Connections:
GND: C1.2, C2.2, Q2.1 (E1), Q2.4 (E2), Q3.1 (E1), Q3.4 (E2), TP7.1, TP8.1, U2.8 (GND), U2.21 (GND)
unnamed: D1.1 (K), Q3.6 (C1)
unnamed: D2.1 (K), Q2.6 (C1)
unnamed: D3.1 (K), Q3.3 (C2)
unnamed: D4.1 (K), Q2.3 (C2)
unnamed: D5.1 (K), R2.1
unnamed: Q1.1 (B), R1.2
unnamed: Q1.3 (C), Q2.2 (B1), Q2.5 (B2), Q3.2 (B1), Q3.5 (B2)
PB0: R1.1, TP1.1, U2.11 (AREF/PB0)
PB1: TP2.1, U2.12 (PB1)
PB2: R2.2, TP3.1, U2.14 (PB2)
PB3: TP4.1, U2.2 (XTAL1/PB3)
PB4: TP5.1, U2.5 (XTAL2/PB4)
PB5: TP6.1, U2.1 (~RESET/PB5)
VCC: C1.1, C2.1, D1.2 (A), D2.2 (A), D3.2 (A), D4.2 (A), D5.2 (A), Q1.2 (E), TP9.1, U2.15 (VCC)

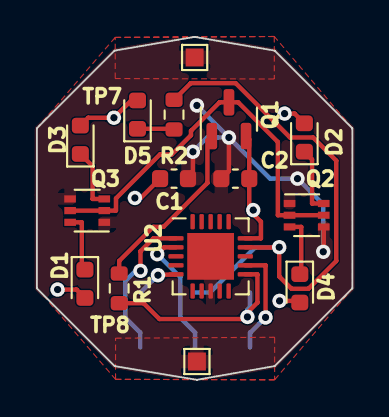
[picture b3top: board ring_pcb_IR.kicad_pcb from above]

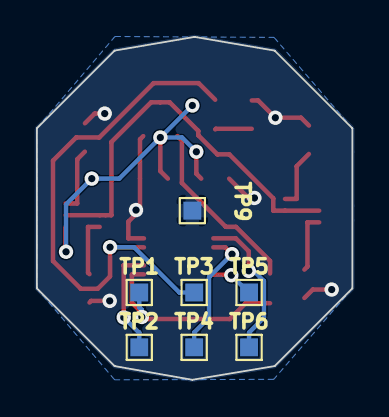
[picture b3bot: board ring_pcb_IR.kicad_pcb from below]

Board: 2 copper layers, 17.5 x 19.1 mm, 22 parts (7 on the bottom side), 15 nets.

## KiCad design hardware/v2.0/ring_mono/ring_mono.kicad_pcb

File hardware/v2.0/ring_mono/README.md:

# Lantern Ring Mono PCB

Production boards use 0.8 mm FR-4, 1 oz copper, and lead-free HASL. Each
assembled variant fits the same LED MPN at D1-D6; TP1 and TP2 are copper
contacts and are not fitted components.

| Variant | LED MPN | Solder mask | Silkscreen |
| --- | --- | --- | --- |
| White / Life | `IN-S126ASUW` | White | Black |
| UV / Death | `SM1206UV-400-IL` | Black | White |
| Red / Rage | `APTL3216SURCK` | Red | White |
| Orange / Avarice | `APTL3216SECK-01` | Yellow | Black |
| Yellow / Fear | `APTL3216SYCK` | Yellow | Black |
| Green / Will | `APTD3216MGC` | Green | White |
| Blue / Hope | `APT3216QBC/D` | Blue | White |
| Indigo / Compassion | `APTR3216-VFX` | Purple | White |
| Pink / Love | `APT3216PBC/RV` | Purple | White |
| Invisible / Infrared | `AP3216F3C` | Black | White |

Orange, indigo, pink, and infrared use the closest available PCB colors.
Confirm exact LED substitutions and fabrication colors before production.

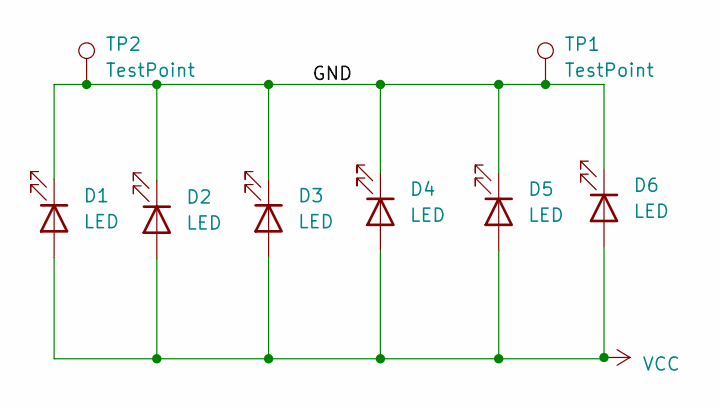
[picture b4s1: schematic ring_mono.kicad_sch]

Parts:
D1, D2, D3, D4, D5, D6: LED; LED_1206_3216Metric
TP1, TP2: TestPoint; TestPoint_Pad_1.5x1.5mm

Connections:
/GND: D1.1 (K), D2.1 (K), D3.1 (K), D4.1 (K), D5.1 (K), D6.1 (K), TP1.1, TP2.1
VCC: D1.2 (A), D2.2 (A), D3.2 (A), D4.2 (A), D5.2 (A), D6.2 (A)

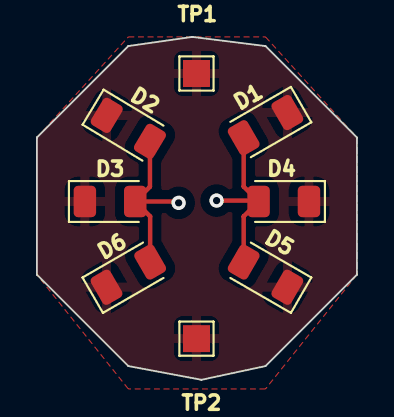
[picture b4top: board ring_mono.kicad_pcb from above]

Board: 2 copper layers, 17.8 x 19.0 mm, 8 parts (0 on the bottom side), 2 nets.

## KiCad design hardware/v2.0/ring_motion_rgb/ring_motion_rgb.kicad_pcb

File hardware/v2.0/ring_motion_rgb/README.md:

# Motion/RGB ring board (prototype baseline)

This is a **separate v2 board variant**; it does not replace or modify
`ring_mono`. The generated PCB preserves the mono board's exact 17.78 x
19.05 mm, 1.6 mm outline and battery-contact copper geometry. It also places
the pogo pads and front-side ground anvil at the same coordinates as the
existing `ring_pcb_IR` programming target, so the current clip can be used
without a new probe guide.

## Proposed circuit

- ATtiny84A-MU (QFN-20), programmed in-circuit through the existing AVR
  ISP-6 clip. The clip-compatible net names `PB0`, `PB1`, `PB2`, and `PB5`
  are **functional ISP aliases**, not the ATtiny84A's native port labels:
  MOSI is PA5, MISO PA6, SCK PA4, and RESET PB3.
- ST LIS2DW12TR accelerometer, I2C mode, with INT1 routed to the MCU. CS is
  tied high, SA0 low (address 0x18), and unused interrupt/NC pads are left
  unconnected.
- One common-cathode Inolux IN-S128TATRGB RGB LED and three 1 kOhm
  current-limit resistors. The shared cathode goes to GND; each MCU output
  sources its channel current through a jumper and resistor.
- Three open solder bridges select the enabled R/G/B channels. This gives
  seven non-zero channel combinations, not arbitrary analog color ratios;
  firmware PWM can tune intensity after the desired channel set is bridged.
- 100 nF local bypass capacitors and a 10 kOhm reset pull-up.

The 1 kOhm LED resistors are a conservative starting point for coin-cell
pulse loading, not a validated current specification. Measure CR2032 voltage
sag, LED current, and cell recovery before choosing production resistor
values or pulse durations.

Primary component references: [ST LIS2DW12 datasheet](https://www.st.com/resource/en/datasheet/lis2dw12.pdf)
and [Inolux IN-S128TATRGB datasheet](https://www.inolux-corp.com/datasheet/SMDLED/RGB%20Top%20View/IN-S128TATRGB_V1.1.pdf).

## Current status

`generate_board.py` creates a **placed, electrically net-assigned, 4-layer
layout baseline** from the existing mono PCB; `generate_schematic.py` creates
the matching KiCad schematic (ERC: 0 errors, 0 warnings, netlist matches the
PCB). The board is **not yet routed** and is not ready to fabricate. The
stackup is F.Cu (GND anvil plane), In1.Cu (signal), In2.Cu (GND plane) and
B.Cu (VCC battery-contact plane). A keepout rule area keeps vias and tracks out
of the exposed rear battery contact. Rules are 0.15 mm track/clearance and
0.5/0.25 mm vias. In particular:

- route the MCU, RGB channels, and sensor bus; refill zones and achieve zero
  DRC errors/unconnected items. `route_ground_first.py` drops every front-side
  GND and VCC SMD pad to the In2.Cu/B.Cu planes with vias, then exports a DSN
  so FreeRouting 2.5.0 (JVM jar) routes the signals around them. That run
  connects all GND and leaves 3 unrouted nets (PB2, PB3, PB5 clip aliases), with
  some narrow-neck, hole-spacing and dangling-via DRC errors. The result is
  saved as `ring_motion_rgb_autoroute_draft.kicad_pcb` for manual cleanup; the
  main `.kicad_pcb` stays unrouted;
- qualify the RGB LED's optical output and current for the transparent crown;
- confirm the LIS2DW12 and ATtiny84A-MU pinouts against the official
  datasheets and vendor package drawings;
- tune the accelerometer wake threshold and pulse/color behavior on the
  assembled ring, then measure CR2032 pulse sag;
- add firmware, BOM fields, and manufacturing checks before release.

The current DRC reports only the unrouted connections (expected before
routing) and two TP1/TP2 footprint-library mismatch warnings, plus an
isolated-copper warning for the In2.Cu ground fill until GND vias connect it. Placement DRC
shows no pad overlaps, but the LED, QFN and 0402 parts are tightly packed. A
FreeCAD STEP fit check found no PCB intersections with the
RingBase, Carrier, ContactDeck, Bezel, or eight crown variants. The minimum
modeled component-to-crown clearance is 0.195 mm. The missing ATtiny84A QFN
STEP model is conservatively represented by a 4 x 4 x 1.0 mm body proxy; this
is a CAD envelope check, not a physical fit or tolerance qualification.

Run generation with KiCad 10's bundled Python and run the interface tests with
system Python:

```powershell
& "C:\Program Files\KiCad\10.0\bin\python.exe" `
  hardware\v2.0\ring_motion_rgb\generate_board.py
python -m unittest discover -s hardware\v2.0\ring_motion_rgb -p "test_*.py"
```

Export the board to STEP and check its fit using FreeCAD's bundled Python:

```powershell
& "C:\Program Files\KiCad\10.0\bin\kicad-cli.exe" pcb export step `
  --output "$env:TEMP\ring_motion_rgb.step" `
  hardware\v2.0\ring_motion_rgb\ring_motion_rgb.kicad_pcb
& "C:\Program Files\FreeCAD 0.19\bin\python.exe" `
  hardware\v2.0\ring_motion_rgb\check_fit.py `
  "$env:TEMP\ring_motion_rgb.step" `
  --json hardware\v2.0\ring_motion_rgb\fit-report.json
```

The interface tests verify outline, battery-contact, programming-pad, and
ground-anvil compatibility. The STEP check validates the current modeled
clearances only; neither tool qualifies electrical routing, clip force, print
tolerances, or physical fit.

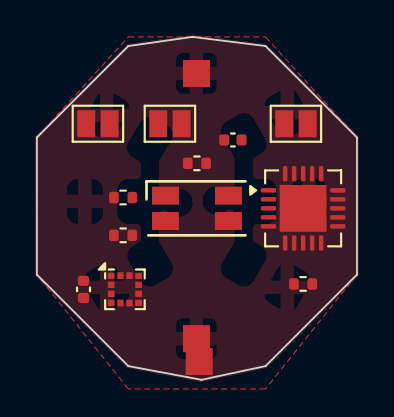
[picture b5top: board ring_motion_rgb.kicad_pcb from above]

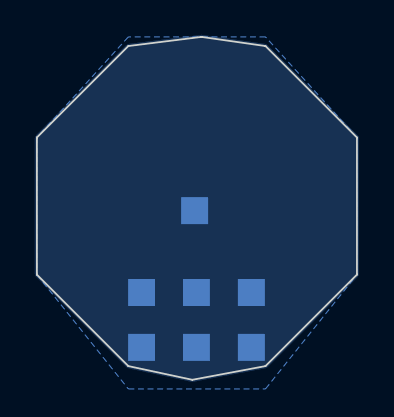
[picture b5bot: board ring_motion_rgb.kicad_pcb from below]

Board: 4 copper layers, 17.8 x 19.0 mm, 22 parts (7 on the bottom side), 20 nets, no tracks yet.

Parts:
C1: 100nF MCU decoupling; C_0402_1005Metric
C2: 100nF accelerometer decoupling; C_0402_1005Metric
D1: IN-S128TATRGB; LED_RGB_1210
J1: R enable; SolderJumper-2_P1.3mm_Open_Pad1.0x1.5mm
J2: G enable; SolderJumper-2_P1.3mm_Open_Pad1.0x1.5mm
J3: B enable; SolderJumper-2_P1.3mm_Open_Pad1.0x1.5mm
P1: PB0; TestPoint_Pad_1.5x1.5mm
P2: PB1; TestPoint_Pad_1.5x1.5mm
P3: PB2; TestPoint_Pad_1.5x1.5mm
P4: PB3; TestPoint_Pad_1.5x1.5mm
P5: PB4; TestPoint_Pad_1.5x1.5mm
P6: PB5; TestPoint_Pad_1.5x1.5mm
P9: VCC; TestPoint_Pad_1.5x1.5mm
R1, R2, R3: 1k; R_0402_1005Metric
R4: 10k RESET pull-up; R_0402_1005Metric
TP1, TP2: TestPoint; TestPoint_Pad_1.5x1.5mm
TP8: GND; TestPoint_Pad_1.5x1.5mm
U1: ATtiny84A-MU; QFN-20-1EP_4x4mm_P0.5mm_EP2.6x2.6mm
U2: LIS2DW12TR; LGA-12_2x2mm_P0.5mm

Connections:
/GND: C1.2, C2.2, D1.2, TP1.1, TP2.1, TP8.1, U1.8, U1.21, U2.1, U2.5, U2.12
ACC_INT: U1.1, U2.9
ACC_SCL: U1.3, U2.3
ACC_SDA: U1.15, U2.6
LED_B: D1.4, R3.2
LED_G: D1.3, R2.2
LED_R: D1.1, R1.2
LIMIT_B: J3.2, R3.1
LIMIT_G: J2.2, R2.1
LIMIT_R: J1.2, R1.1
PB0: P1.1, U1.11
PB1: P2.1, U1.12
PB2: P3.1, U1.14
PB3: P4.1, U1.20
PB4: P5.1, U1.16
PB5: P6.1, R4.1, U1.13
PWM_B: J3.1, U1.2
PWM_G: J2.1, U1.4
PWM_R: J1.1, U1.5
VCC: C1.1, C2.1, P9.1, R4.2, U1.9, U2.4, U2.10, U2.11

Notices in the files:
hardware/v2.0/ring_pcb_RGBW_dual/README.md:
repository's TAPR open-hardware licence. Manufacturer datasheets are linked,
